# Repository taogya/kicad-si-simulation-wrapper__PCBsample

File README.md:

# kicad-si-simulation-wrapper__PCBsample
sample pcb for kicad-si-simulation-wrapper

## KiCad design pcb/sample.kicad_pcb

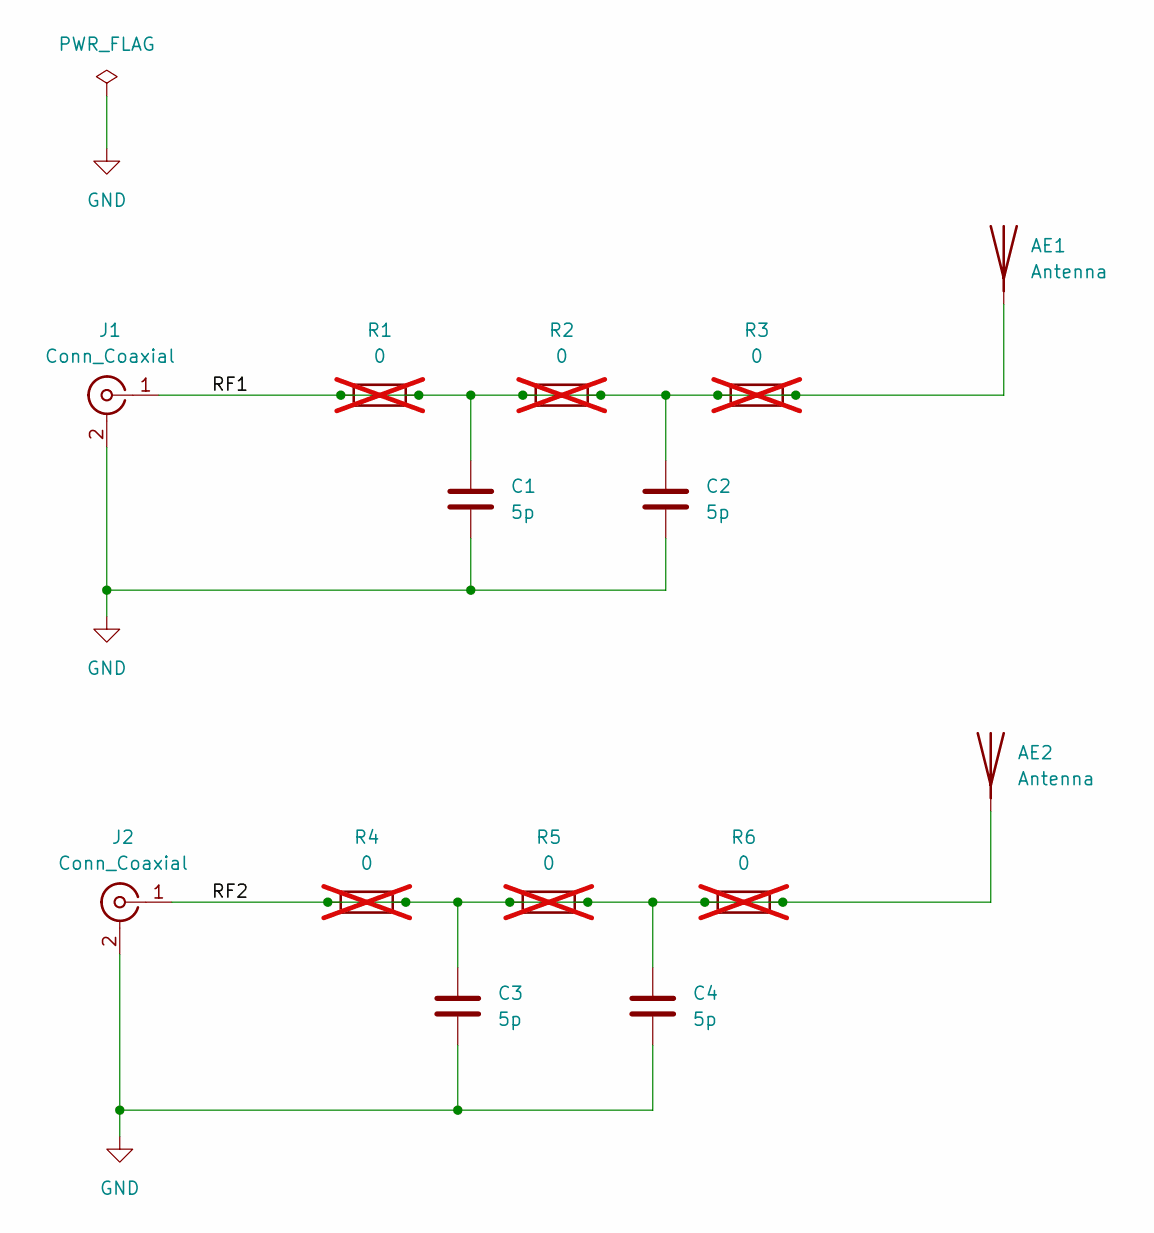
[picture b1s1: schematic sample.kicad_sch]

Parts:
AE1: Antenna; Antenna_Stub_1.0mm
AE2: Antenna; Antenna_Stub_0.5mm
C1, C2, C3, C4: 5p; C_0402_1005Metric
J1, J2: Conn_Coaxial; SMA_Molex_73251-2200_Horizontal
R1, R2, R3, R4, R5, R6: 0; R_0402_1005Metric; not fitted

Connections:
/RF1: AE1.1 (A), C1.1, C2.1, J1.1 (In), R1.1, R1.2, R2.1, R2.2, R3.1, R3.2
/RF2: AE2.1 (A), C3.1, C4.1, J2.1 (In), R4.1, R4.2, R5.1, R5.2, R6.1, R6.2
GND: C1.2, C2.2, C3.2, C4.2, J1.2 (Ext), J2.2 (Ext)

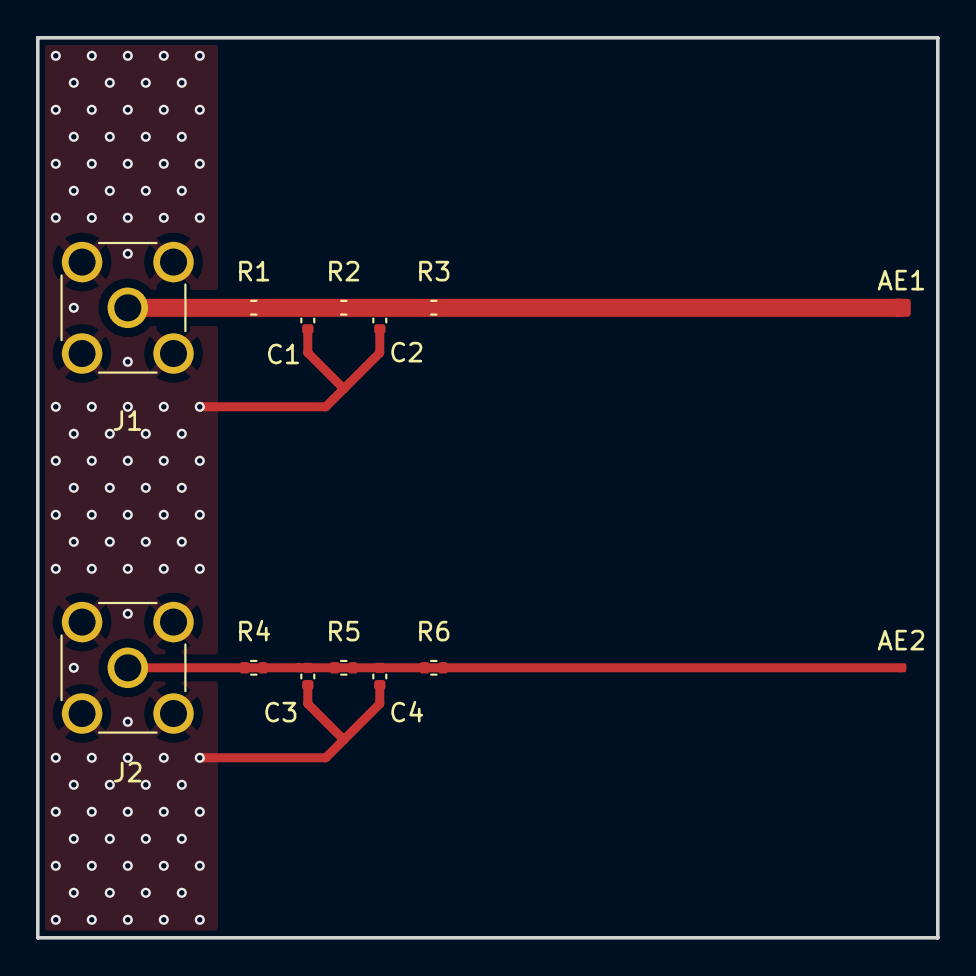
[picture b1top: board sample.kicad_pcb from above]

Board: 2 copper layers, 50.0 x 50.0 mm, 14 parts (0 on the bottom side), 3 nets.

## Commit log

2025-05-21 add pcb
2025-05-25 apply output pos file
2025-05-26 modify KiCAD 9.0 to 8.0
2025-05-27 fix debug.py (change offset)
2025-05-28 modify debug.py, add simulation.py
2025-05-29 modify debug.py
